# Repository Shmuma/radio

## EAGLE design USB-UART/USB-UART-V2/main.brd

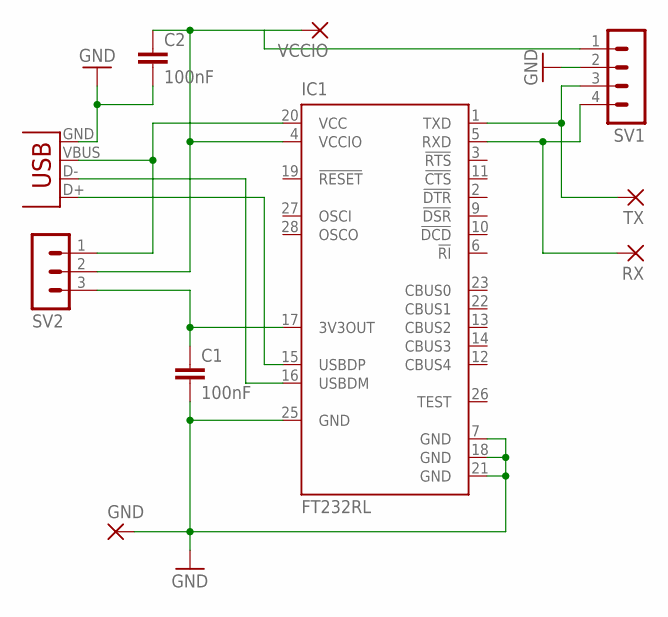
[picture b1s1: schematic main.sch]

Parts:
C1, C2: 100nF; C0805
GND: WIREPADSMD1,27-254; SMD1,27-2,54
IC1: FT232RL; SSOP28
RX: WIREPADSMD1,27-254; SMD1,27-2,54
SV1: MA04-1
SV2: MA03-1
TX: WIREPADSMD1,27-254; SMD1,27-2,54
VCCIO: WIREPADSMD1,27-254; SMD1,27-2,54
X1: USB-MICROB

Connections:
GND: C1.2, C2.2, GND.1, IC1.7 (GND), IC1.18 (GND), IC1.21 (GND), IC1.25 (GND), SV1.2, X1.GND
unnamed: C1.1, IC1.17 (3V3OUT), SV2.3
unnamed: IC1.15 (USBDP), X1.D+
unnamed: IC1.16 (USBDM), X1.D-
unnamed: C2.1, IC1.4 (VCCIO), SV1.1, SV2.2, VCCIO.1
unnamed: IC1.20 (VCC), SV2.1, X1.VBUS
unnamed: IC1.1 (TXD), SV1.3, TX.1
unnamed: IC1.5 (RXD), RX.1, SV1.4

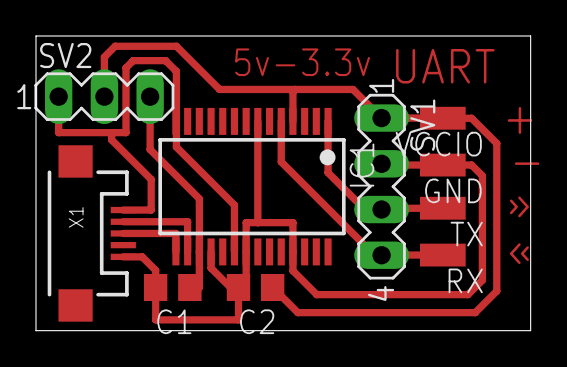
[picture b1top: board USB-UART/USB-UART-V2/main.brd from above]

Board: 2 copper layers, 27.5 x 16.4 mm, 10 parts (0 on the bottom side), 8 nets.

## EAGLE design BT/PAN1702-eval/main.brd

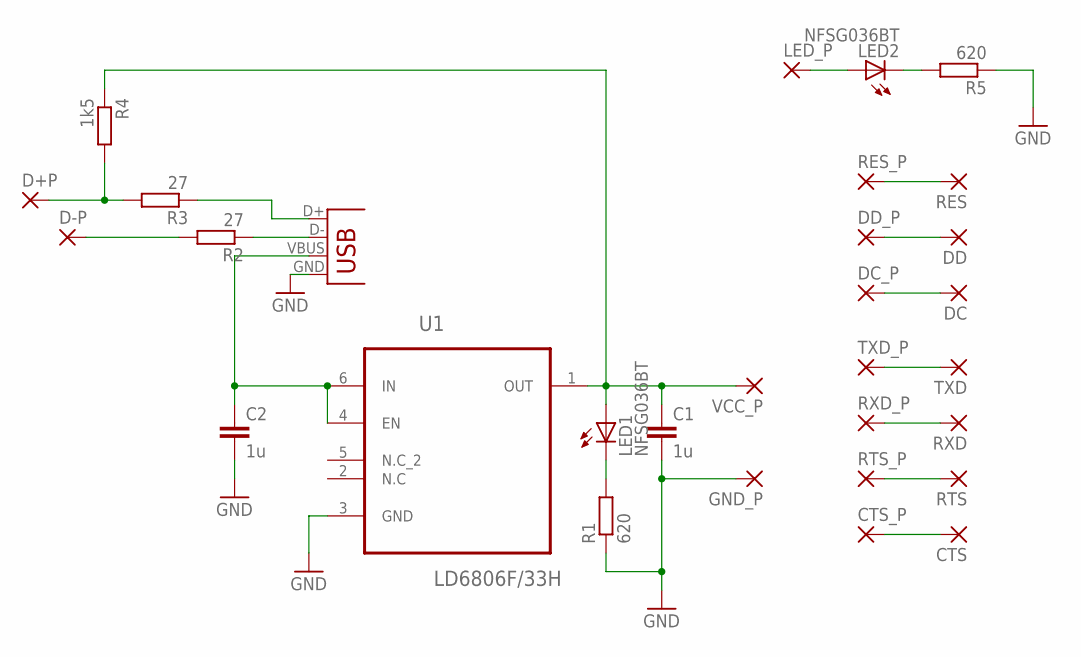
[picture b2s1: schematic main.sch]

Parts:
C1, C2: 1u; C0805
CTS: WIREPAD1,6/0,8; 1,6/0,8
CTS_P: WIREPAD1,6/0,8; 1,6/0,8
D+P: WIREPAD1,6/0,8; 1,6/0,8
D-P: WIREPAD1,6/0,8; 1,6/0,8
DC: WIREPAD1,6/0,8; 1,6/0,8
DC_P: WIREPAD1,6/0,8; 1,6/0,8
DD: WIREPAD1,6/0,8; 1,6/0,8
DD_P: WIREPAD1,6/0,8; 1,6/0,8
GND_P: WIREPAD1,6/0,8; 1,6/0,8
LED1, LED2: NFSG036BT
LED_P: WIREPAD1,6/0,8; 1,6/0,8
R1, R5: 620; R0805
R2, R3: 27; R0805
R4: 1k5; R0805
RES: WIREPAD1,6/0,8; 1,6/0,8
RES_P: WIREPAD1,6/0,8; 1,6/0,8
RTS: WIREPAD1,6/0,8; 1,6/0,8
RTS_P: WIREPAD1,6/0,8; 1,6/0,8
RXD: WIREPAD1,6/0,8; 1,6/0,8
RXD_P: WIREPAD1,6/0,8; 1,6/0,8
TXD: WIREPAD1,6/0,8; 1,6/0,8
TXD_P: WIREPAD1,6/0,8; 1,6/0,8
U1: LD6806F/33H; SON50P100X145X50-6N
VCC_P: WIREPAD1,6/0,8; 1,6/0,8
X1: USB-MICROB

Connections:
3V3: C1.1, LED1.A, R4.1, U1.1 (OUT), VCC_P.1
5V: C2.1, U1.4 (EN), U1.6 (IN), X1.VBUS
GND: C1.2, C2.2, GND_P.1, R1.1, R5.1, U1.3 (GND), X1.GND
unnamed: D+P.1, R3.2, R4.2
unnamed: R3.1, X1.D+
unnamed: DD.1, DD_P.1
unnamed: DC.1, DC_P.1
unnamed: TXD.1, TXD_P.1
unnamed: RXD.1, RXD_P.1
unnamed: RTS.1, RTS_P.1
unnamed: CTS.1, CTS_P.1
unnamed: LED1.C, R1.2
unnamed: R2.1, X1.D-
unnamed: D-P.1, R2.2
unnamed: LED2.A, LED_P.1
unnamed: LED2.C, R5.2
unnamed: RES.1, RES_P.1

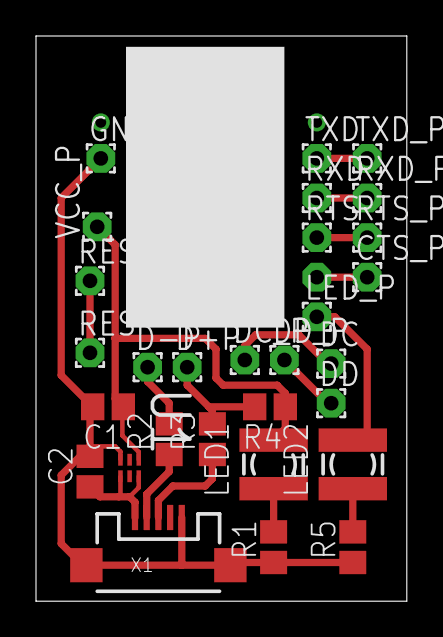
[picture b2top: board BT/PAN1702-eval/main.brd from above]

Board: 2 copper layers, 20.6 x 31.4 mm, 30 parts (1 on the bottom side), 17 nets.

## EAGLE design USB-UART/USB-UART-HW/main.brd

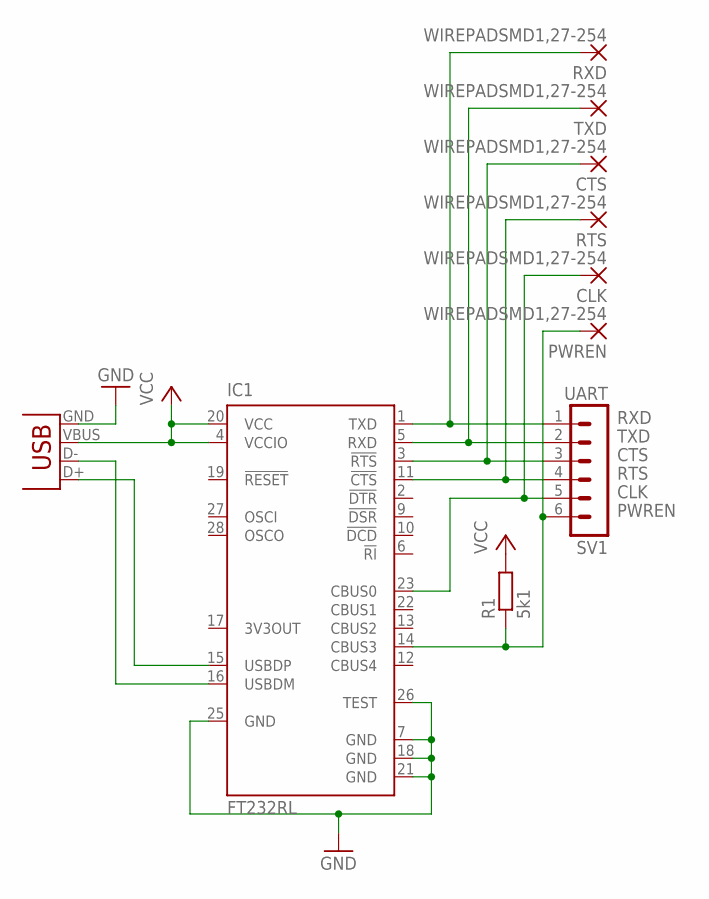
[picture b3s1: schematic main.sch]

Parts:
CLK: WIREPADSMD1,27-254; SMD1,27-2,54
CTS: WIREPADSMD1,27-254; SMD1,27-2,54
IC1: FT232RL; SSOP28
PWREN: WIREPADSMD1,27-254; SMD1,27-2,54
R1: 5k1; R0805
RTS: WIREPADSMD1,27-254; SMD1,27-2,54
RXD: WIREPADSMD1,27-254; SMD1,27-2,54
SV1: UART; MA06-1
TXD: WIREPADSMD1,27-254; SMD1,27-2,54
X1: USB-MICROB

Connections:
CLK: CLK.1, IC1.23 (CBUS0), SV1.5
CTS: CTS.1, IC1.3 (!RTS), SV1.3
GND: IC1.7 (GND), IC1.18 (GND), IC1.21 (GND), IC1.25 (GND), IC1.26 (TEST), X1.GND
unnamed: IC1.15 (USBDP), X1.D+
unnamed: IC1.16 (USBDM), X1.D-
PWREN: IC1.14 (CBUS3), PWREN.1, R1.1, SV1.6
RTS: IC1.11 (!CTS), RTS.1, SV1.4
RXD: IC1.1 (TXD), RXD.1, SV1.1
TXD: IC1.5 (RXD), SV1.2, TXD.1
VCC: IC1.4 (VCCIO), IC1.20 (VCC), R1.2, X1.VBUS

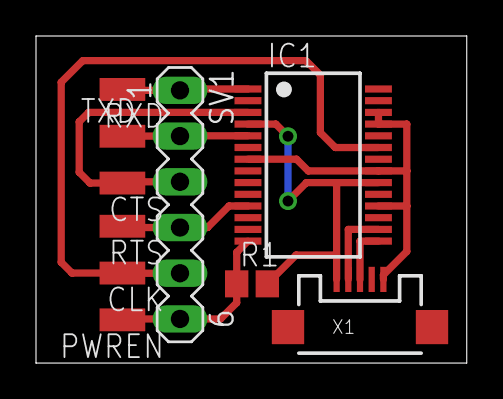
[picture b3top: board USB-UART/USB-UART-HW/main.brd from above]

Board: 2 copper layers, 23.9 x 18.2 mm, 10 parts (0 on the bottom side), 10 nets.

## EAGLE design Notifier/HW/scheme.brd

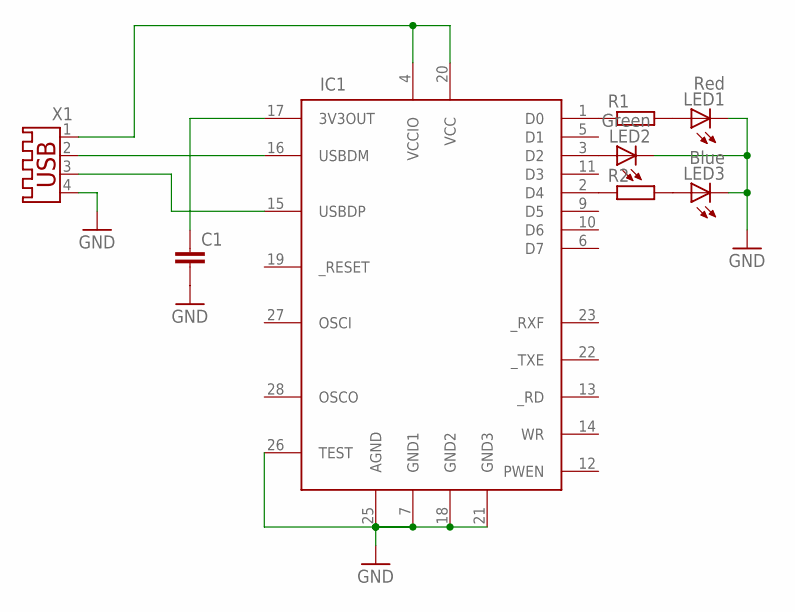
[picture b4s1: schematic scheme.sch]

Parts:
C1: C-EUC0805; C0805
IC1: FT245RL; SSOP28DB
LED1: Red; LED5MM
LED2: Green; LED5MM
LED3: Blue; LED3MM
R1, R2: R-EU_0204/5; 0204/5
X1: USB-A003

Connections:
GND: C1.2, IC1.7 (GND1), IC1.18 (GND2), IC1.21 (GND3), IC1.25 (AGND), IC1.26 (TEST), LED1.K (C), LED2.K (C), LED3.K (C), X1.4
unnamed: IC1.4 (VCCIO), IC1.20 (VCC), X1.1
unnamed: IC1.16 (USBDM), X1.2
unnamed: IC1.15 (USBDP), X1.3
unnamed: IC1.1 (D0), R1.1
unnamed: IC1.2 (D4), R2.1
unnamed: IC1.3 (D2), LED2.A
unnamed: LED3.A, R2.2
unnamed: LED1.A, R1.2
unnamed: C1.1, IC1.17 (3V3OUT)

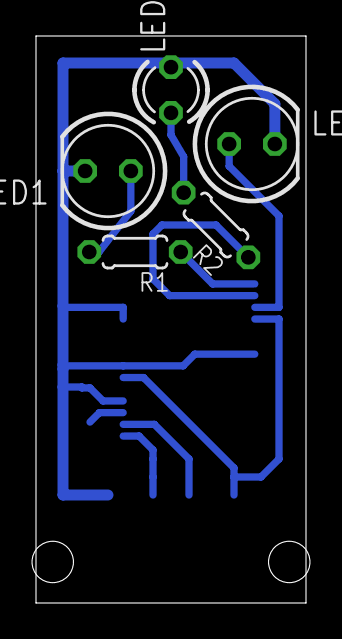
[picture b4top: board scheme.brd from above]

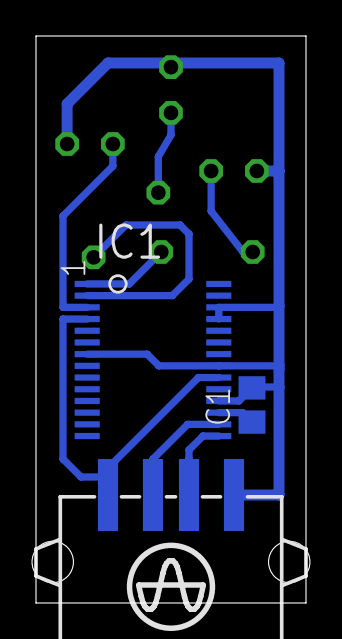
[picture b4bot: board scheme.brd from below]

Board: 2 copper layers, 15.0 x 31.5 mm, 8 parts (3 on the bottom side), 10 nets.

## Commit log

2010-09-13 Microphone preamp started.
2010-09-13 Start from scratch
2010-09-13 Schematic finished
2010-09-14 Clearance
2010-09-17 Preamp LTSpice simulation
2010-09-26 Microphone preamp finished and working.
    http://blog.shmuma.ru/2010/09/26/%D0%B8%D0%B7%D0%B4%D0%B5%D0%BB%D0%B8%D0%B5-%E2%84%961/
2010-09-27 uJDM programmator started
2010-09-27 Rippler and transistor simulation
2010-09-27 uJDB board
2010-10-06 Board finished
2010-10-06 Ping-pong game started
2010-10-07 ping-poig schematic (finished) and board (started)
2010-10-07 Layout of ping-pong finished
2010-10-07 Ping-pong board ready
2010-10-08 Minor fixes
2010-10-11 Optmize board
2010-10-12 uJDM board ready
2010-10-13 minor
2010-10-13 Ping-pong needs reroute
2010-10-13 ping-pong board, cont
2010-10-14 Make board for ping-pong
2010-10-16 fix programmator a little
2010-10-24 DB9 pinout image
2010-11-02 Data copy program, valid version.
2010-11-06 Ping-Pong program complete.
2010-11-07 Random led program. Started.
2010-11-08 Random program
2010-11-10 Random works
2010-11-11 PIC USB started
2010-11-12 USB programmator, cont
2010-11-12 Started to route adapter
2010-11-12 Adapter board finished
2010-11-12 Adabter board finished
2010-11-12 Programmator started
2010-11-13 Programmer scheme finished
2010-11-13 USB PIC board draft
2010-11-14 USB PIC board finished
2010-11-14 Small board fixes
2010-11-22 small fix project
2010-11-28 ART2003 started
2010-11-28 ART2003 ready
2010-11-30 ART2003
2010-12-03 RC integrator and differentiator
2010-12-06 Decided to make GTP-uSB work on linux
2010-12-12 Several simulations added
2010-12-16 gtp programmator tool started
2010-12-17 [gtp] Find device
2010-12-18 Dir reorganization
2010-12-18 Simplify device descovery
2010-12-18 Device version success
2010-12-20 PICKit2 adapter connector started
2010-12-21 Trying to read chip's content
2010-12-21 dump data
2010-12-22 PicKit2 labs
2010-12-26 Lab2 mod
2010-12-26 Lab3 done
2010-12-26 Lab4 done - use ADC
2010-12-26 Started to reverse PIC detection
2010-12-30 New eagle
2010-12-31 USB-LCD demo started
2011-01-01 PIC LCD-USB demo finished
2011-01-08 Timer lab
2011-01-08 Clock control added
2011-01-10 Fixed LCD board wiring mistakes. It works now.
2011-01-13 LCD MCU control, started
2011-01-15 Delay loops
2011-01-15 Cannnot clear LCD
2011-01-15 LCD cleared after a long while. Need to check busy flag
2011-01-15 Busy flag added
2011-01-15 Works a little
2011-01-17 Needs timing optimization
2011-01-18 C for PIC
2011-01-19 Minor fix
2011-01-19 Base-C: imported xlcd
2011-01-19 Timings optimized
2011-01-23 18F2550 USB initialization
2011-01-26 LCD C control. Not working os far.
2011-01-26 LCD works
2011-01-26 Lost files
2011-01-29 Strange bits state
2011-01-30 Check USB status on LCD. Works.
2011-01-30 Bin changed
2011-01-30 Trying to find USB error. Unsuccessfull so far.
2011-02-05 CCS compiler is really great
2011-02-05 Enum process finished
2011-02-06 Data exchange working
2011-02-06 LCD USB clock (trivial)
2011-02-22 PingPong finished
2011-03-04 Light sensor
2011-03-17 Clock schematic started
2011-05-15 Misc simulations
2012-10-28 Notifier, v1
2012-12-04 DCF77-44pin
2012-12-05 Interrupts mess
2012-12-07 Need uart to get full sequence
2012-12-07 USB-UARD scheme and board
2012-12-18 UART
2012-12-18 DCF77 protocol logger
2012-12-22 Ready to decode bits
2012-12-22 Pullup didn't help much
2012-12-23 Decode tools
2012-12-23 Join of events
2012-12-24 Dump sampled data
2012-12-24 Dump raw data, sampled every 1ms
2012-12-25 DCF77 is a crap
2013-01-07 BT Pan1702 eval board
2013-01-07 RF sniffer started
2013-01-07 Misc changes
2016-05-24 Latest
2016-05-25 Button led test
2016-12-03 Dot matrix simple shell clock

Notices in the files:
parts and their libraries:
SparkFun: Licensing: CC v3.0 Share-Alike You are welcome to use this library for commercial purposes.
